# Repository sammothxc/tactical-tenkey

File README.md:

# tactical-tenkey
A tactile, tactical tenkey that doubles as a USB/BT numpad

## TODO
- [ ] fix menu timeout glitch
- [ ] fix battery level
- [ ] fix pairing error (bt, linux)

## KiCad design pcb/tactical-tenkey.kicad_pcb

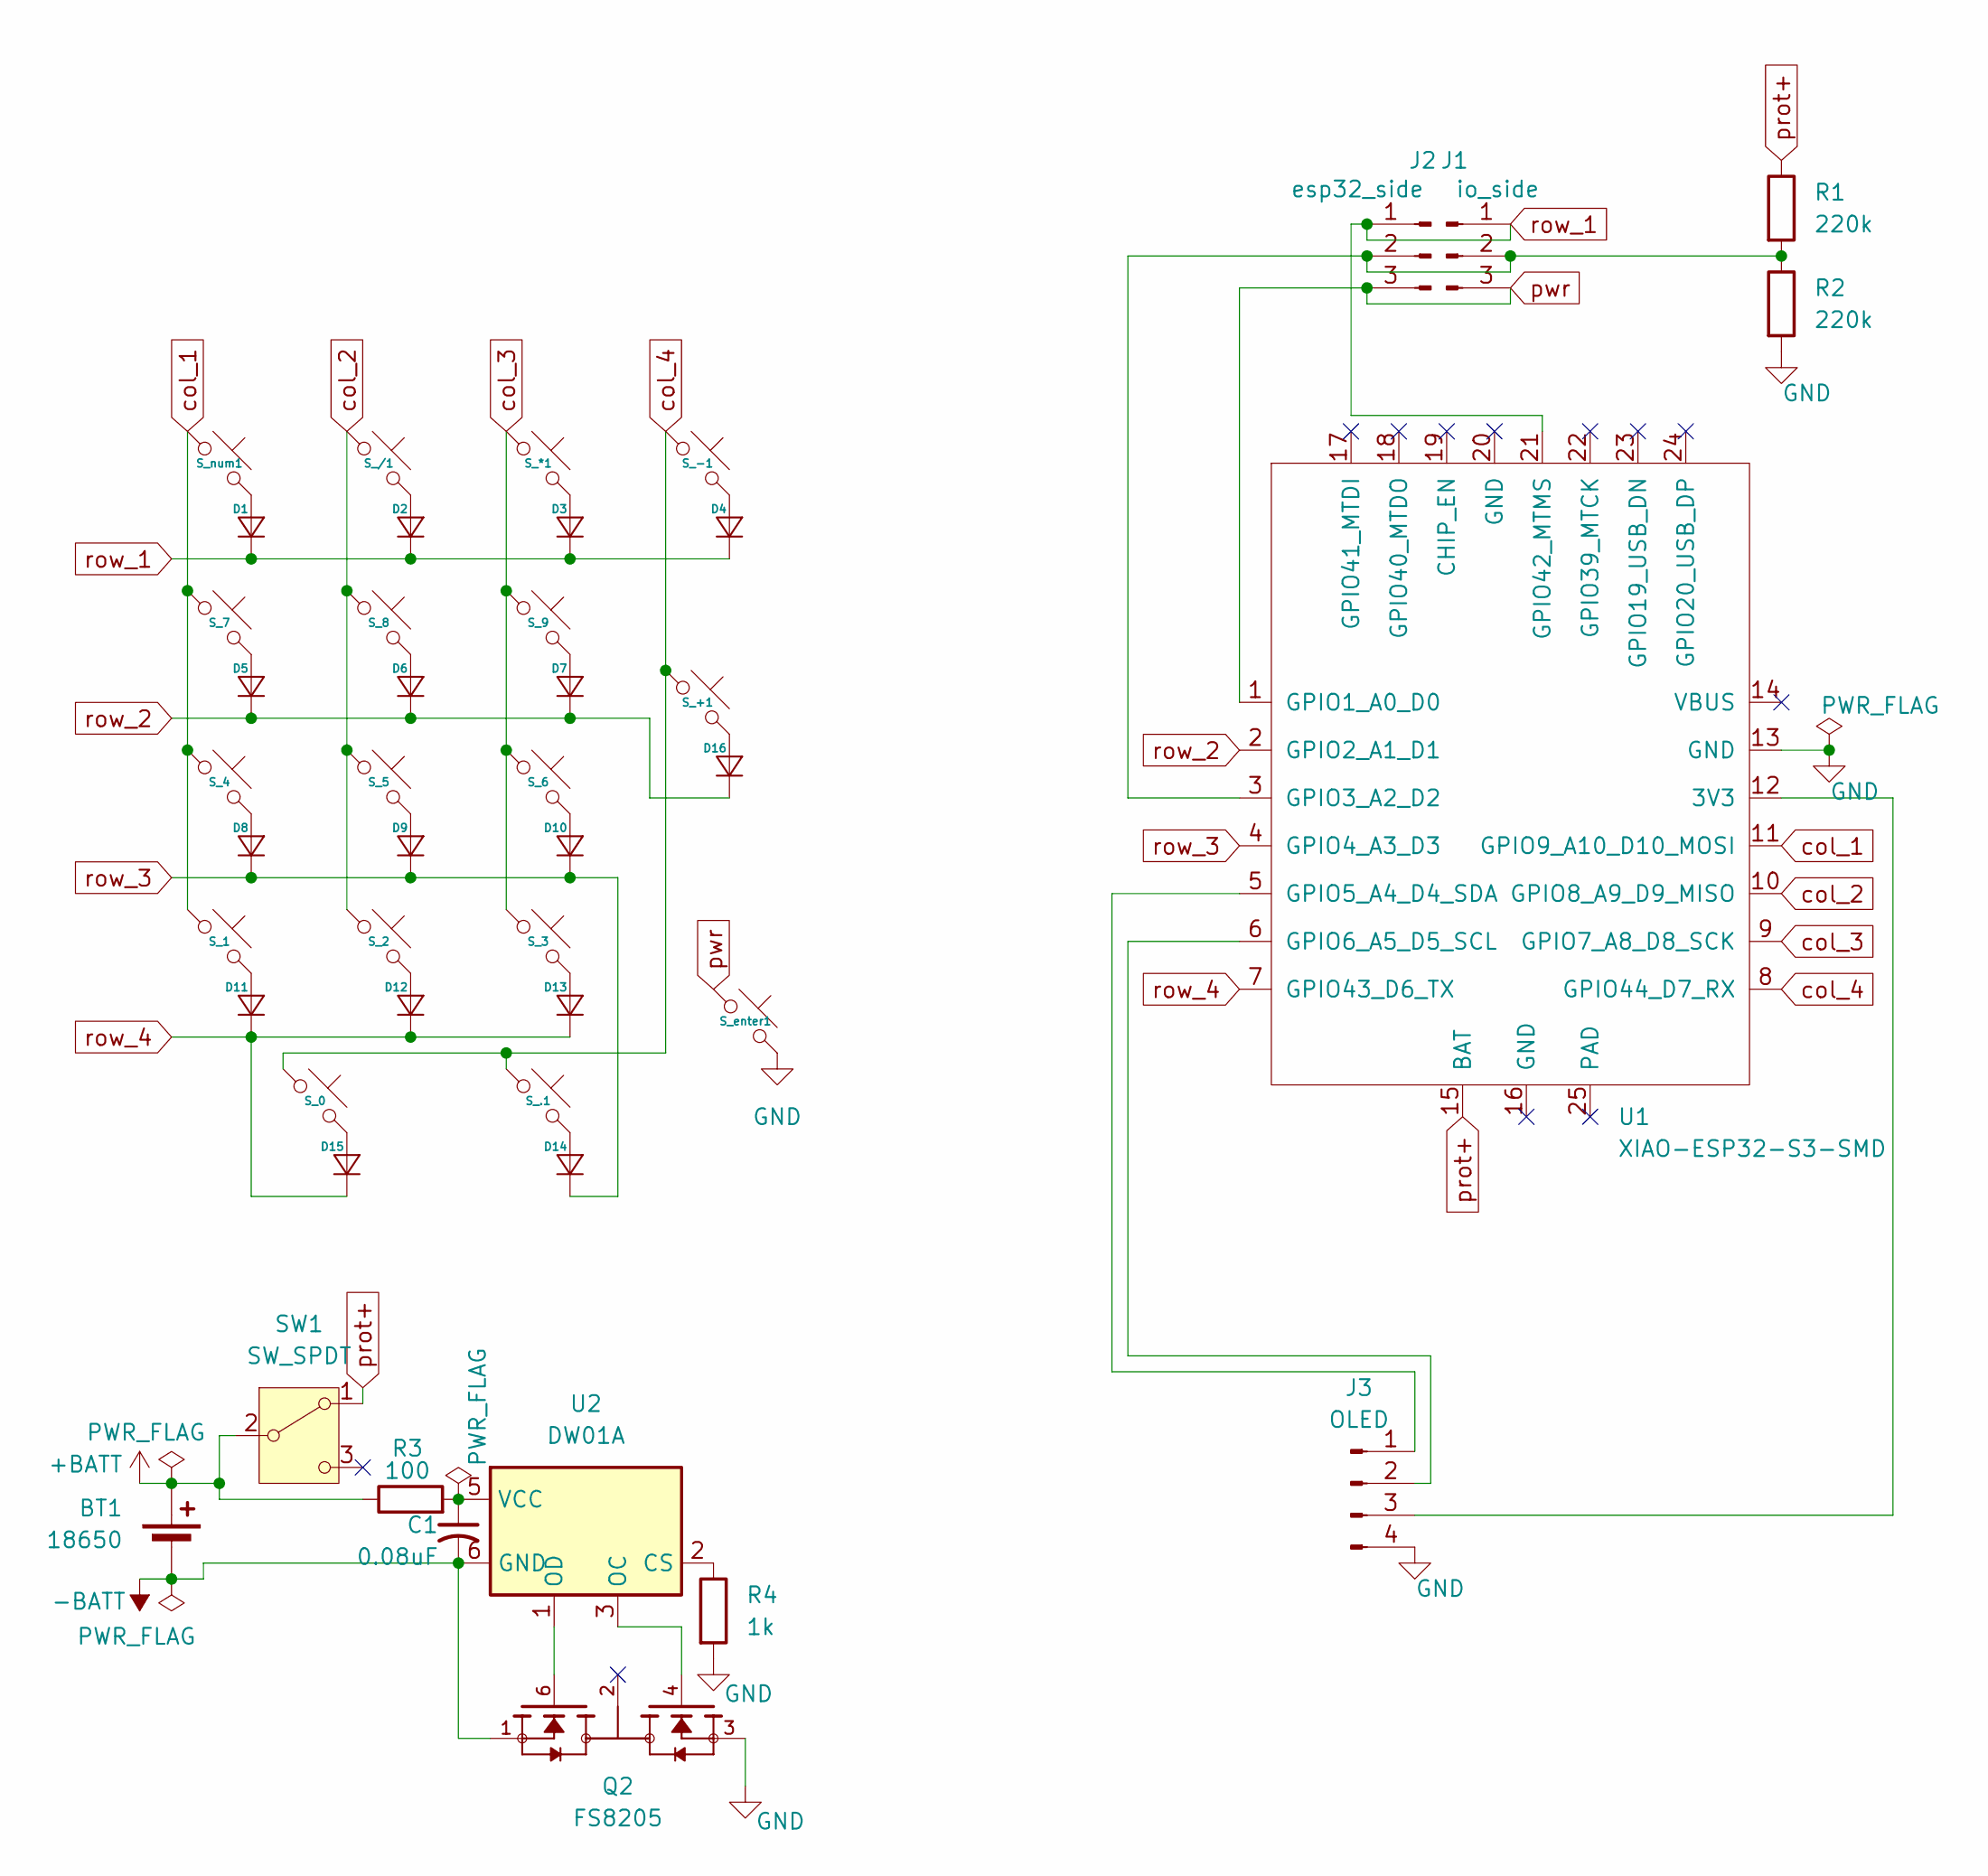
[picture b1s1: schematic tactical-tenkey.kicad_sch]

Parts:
BT1: 18650; PinHeader_1x02_P2.54mm_Vertical
C1: 0.08uF; CP_Radial_Tantal_D4.5mm_P5.00mm
D1, D2, D3, D4, D5, D6, D7, D8, D9, D10, D11, D12, D13, D14, D15, D16: Diode_DO-35
J1: io_side; PinHeader_1x03_P2.54mm_Vertical
J2: esp32_side; PinHeader_1x03_P2.54mm_Vertical
J3: OLED; PinHeader_1x04_P2.54mm_Vertical
Q2: FS8205; SOT95P280X145-6N; PARTREV 1.9
R1, R2: 220k; R_Axial_DIN0207_L6.3mm_D2.5mm_P10.16mm_Horizontal
R3: 100; R_Axial_DIN0207_L6.3mm_D2.5mm_P10.16mm_Horizontal
R4: 1k; R_Axial_DIN0207_L6.3mm_D2.5mm_P10.16mm_Horizontal
SW1: SW_SPDT; SS-12F23G5
S_0: Hotswap_MX_Plated_2.00u
S_1, S_2, S_3, S_4, S_5, S_6, S_7, S_8, S_9, S_.1: Hotswap_MX_Plated_1.00u
S_*1: Hotswap_MX_Plated_1.00u
S_+1: Hotswap_MX_Plated_2.00u
S_-1: Hotswap_MX_Plated_1.00u
S_/1: Hotswap_MX_Plated_1.00u
S_enter1: Hotswap_MX_Plated_2.00u
S_num1: Hotswap_MX_Plated_1.00u
U1: XIAO-ESP32-S3-SMD; XIAO-ESP32-S3-SMD_PAD
U2: DW01A; SOT-23-6

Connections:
+BATT: BT1.1 (+), R3.1, SW1.2 (B)
-BATT: BT1.2 (-), C1.2, Q2.1, U2.6 (GND)
GND: J3.4, Q2.3, R2.2, R4.2, S_enter1.2, U1.13 (GND)
unnamed: D1.2 (A), S_num1.2
unnamed: D2.2 (A), S_/1.2
unnamed: D3.2 (A), S_*1.2
unnamed: D4.2 (A), S_-1.2
unnamed: D5.2 (A), S_7.2
unnamed: D6.2 (A), S_8.2
unnamed: D7.2 (A), S_9.2
unnamed: D8.2 (A), S_4.2
unnamed: D9.2 (A), S_5.2
unnamed: D10.2 (A), S_6.2
unnamed: D11.2 (A), S_1.2
unnamed: D12.2 (A), S_2.2
unnamed: D13.2 (A), S_3.2
unnamed: D14.2 (A), S_.1.2
unnamed: D15.2 (A), S_0.2
unnamed: D16.2 (A), S_+1.2
unnamed: J1.2, J2.2, R1.2, R2.1, U1.3 (GPIO3_A2_D2)
unnamed: J3.1, U1.5 (GPIO5_A4_D4_SDA)
unnamed: J3.2, U1.6 (GPIO6_A5_D5_SCL)
unnamed: J3.3, U1.12 (3V3)
unnamed: R4.1, U2.2 (CS)
unnamed: Q2.4, U2.3 (OC)
unnamed: Q2.6, U2.1 (OD)
unnamed: C1.1, R3.2, U2.5 (VCC)
col_1: S_1.1, S_4.1, S_7.1, S_num1.1, U1.11 (GPIO9_A10_D10_MOSI)
col_2: S_2.1, S_5.1, S_8.1, S_/1.1, U1.10 (GPIO8_A9_D9_MISO)
col_3: S_3.1, S_6.1, S_9.1, S_*1.1, U1.9 (GPIO7_A8_D8_SCK)
col_4: S_0.1, S_+1.1, S_-1.1, S_.1.1, U1.8 (GPIO44_D7_RX)
prot+: R1.1, SW1.1 (A), U1.15 (BAT)
pwr: J1.3, J2.3, S_enter1.1, U1.1 (GPIO1_A0_D0)
row_1: D1.1 (K), D2.1 (K), D3.1 (K), D4.1 (K), J1.1, J2.1, U1.21 (GPIO42_MTMS)
row_2: D5.1 (K), D6.1 (K), D7.1 (K), D16.1 (K), U1.2 (GPIO2_A1_D1)
row_3: D8.1 (K), D9.1 (K), D10.1 (K), D14.1 (K), U1.4 (GPIO4_A3_D3)
row_4: D11.1 (K), D12.1 (K), D13.1 (K), D15.1 (K), U1.7 (GPIO43_D6_TX)

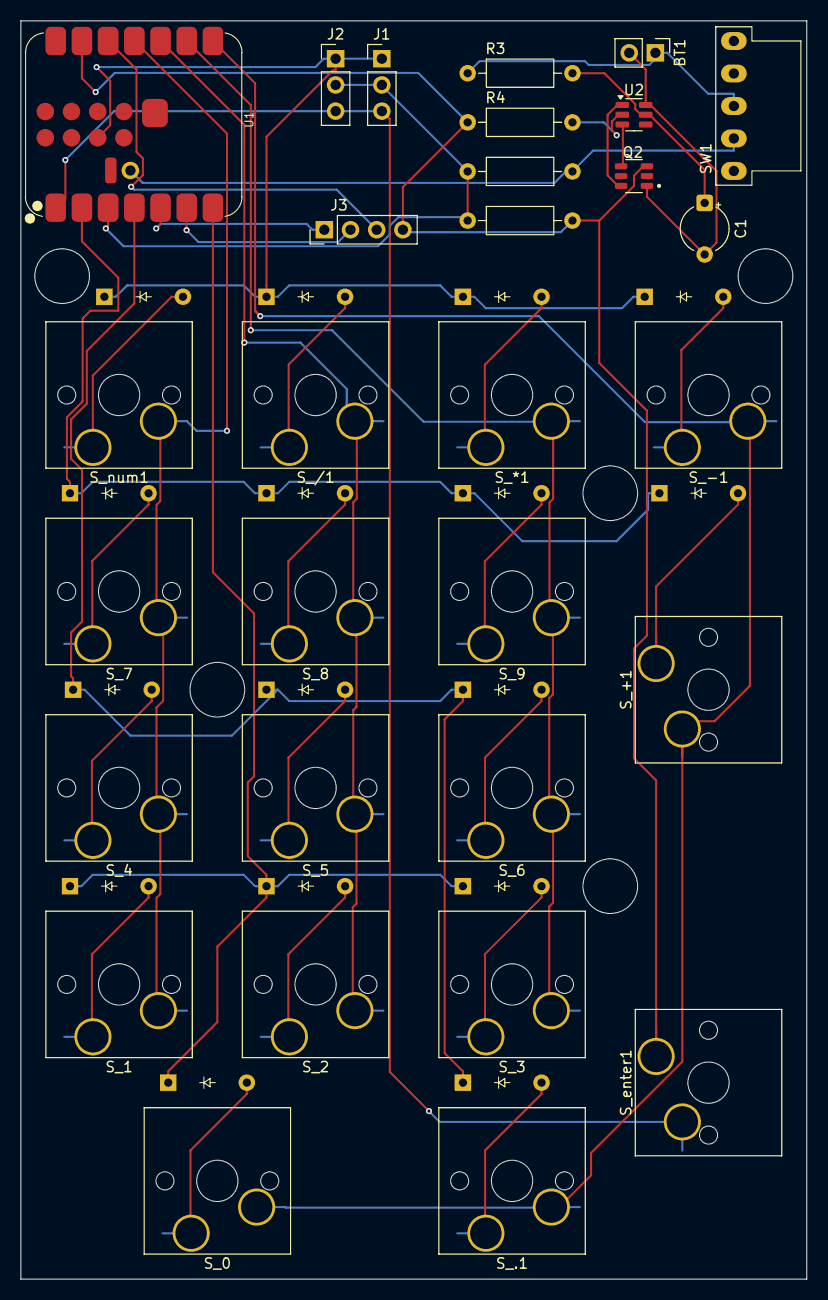
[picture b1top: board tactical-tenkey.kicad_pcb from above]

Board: 2 copper layers, 76.2 x 122.0 mm, 46 parts (0 on the bottom side), 37 nets.

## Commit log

2026-02-05 Add license
2026-02-10 blink
2026-02-10 very basic math prototype
2026-02-10 edits
2026-02-11 refactor and add bottom status bar
2026-02-11 clear key behavior and fn combo logic
2026-02-11 icons
2026-02-11 bottom bar logic
2026-02-11 versioning
2026-02-11 bootscreen
2026-02-11 file restructure
2026-02-11 macro state machine
2026-02-11 macro menu
2026-02-11 usb numpad mode and send answer feature
2026-02-11 change keybinds
2026-02-11 file structuring
2026-02-12 rest in peace, esp32c6 doesn't have USB HID capability so esp32c3 it is
2026-02-12 dev board pins
2026-02-16 .gitignore
2026-02-16 pcb boilerplate
2026-02-16 schematic
2026-02-16 battery protection
2026-02-16 xiao esp32s3
2026-02-16 boot logo
2026-02-16 add boot logo
2026-02-16 correct led pin
2026-02-16 auto versioning
2026-02-16 versioning and boot screen welcome
2026-02-16 welcome guide
2026-02-17 pcb layout
2026-02-17 routing
2026-02-26 case
2026-02-26 working on the case
2026-03-09 fix stabilizer orientation on plate
2026-03-09 case development
2026-03-10 fs8205
2026-03-10 footprint and pcb final edits (pre silkscreen art)
2026-03-11 final pcb touches
2026-03-11 Add GNU GPL v3 license
    Added the GNU General Public License version 3 to the project.
2026-03-11 final pcb touches for real this time
2026-03-28 flip display, use pin 3 for row 1
2026-04-01 firmware.bin build script
2026-04-20 menu fix
2026-04-22 build_scripts
2026-04-23 fix battery mgmt not working after switching off
2026-04-24 major progress: help pages rework, numpad mode functional, macro menu combo fix, toggleable nav/num mode, and send result function fixed
2026-04-24 github action set up to automate compiling a release firmware
2026-04-24 build release on each commit
2026-04-24 version updates
2026-04-24 release.yml fixed
2026-04-24 version fixes
2026-04-24 retire firmware.json
2026-04-24 testing complete
2026-04-25 quick binds, settings menu, ui glitch fixes, and clear key bug fixes
2026-04-25 factory defaults settings option, ble settings menu,
2026-04-25 settings bug fix
2026-04-25 macro fix. ble coming soon to theaters near u
2026-04-25 HID dispatcher refactor
2026-04-25 hid pt 2
2026-04-25 ble connection init
2026-04-25 ble ui boilerplate
2026-04-25 ditch nimble for bluedroid
2026-04-26 fix ble on macos, nameless listing on linux, and add zoom in/out functionality in numpad nav mode
2026-04-26 fix zomm in/out on macos with zoom modifier settings option
2026-04-26 fix linux bt connection issues
2026-04-28 bottom plate ncn code
2026-05-18 t2-firmware-app
2026-05-18 t2-fw-app edits
2026-05-18 fw app fixes
2026-05-18 fw app workflow edits
2026-05-24 case edits
2026-05-29 t2 firmware app updates
2026-05-29 ci/cd fixes
2026-05-29 fw app edits
2026-05-29 changelog fix
2026-05-29 bump release tag
2026-05-29 more firmware app edits
2026-05-29 cors errors
2026-05-29 migrate firmware app to cloudflare pages
2026-05-29 even more firmware app edits
2026-05-29 cf pages rebuild
2026-05-29 fix cors error
2026-05-29 flash offset error
2026-05-30 fix firmware app offset, firmware.bin now includes all partitions
2026-05-30 trigger firmware rebuild
2026-05-30 fix issue where 5 was firing on-release instead of on-press
2026-05-30 fix BLE advertisement, now pairs with windows
2026-05-31 fix numpad keys to be numlock independent
2026-05-31 fix cursor movement on windows and mac, and add host os icon to status bar
2026-05-31 TODO edits
2026-05-31 fix number keys not working in BLE mode on windows
2026-05-31 v1 released! celebrating bug-free bluetooth!!
2026-05-31 battery level implementation in progress, and settings edits
2026-05-31 quick bind macro key fire logic fix
2026-06-15 front plate edits
